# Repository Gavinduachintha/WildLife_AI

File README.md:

<div align="center">

# WildLife AI

</div>

## Introduction

WildLife AI is a prototype edge-computing system for monitoring remote forest environments. It uses computer vision on a Raspberry Pi 5 to identify objects or activities of interest, obtains the monitoring node's geographic position through a GPS module, and transmits a compact alert over a LoRa link.

The receiving station is based on a Raspberry Pi Pico 2. It receives the alert and presents the detected object, confidence value, geographic coordinates, and communication status on an IPS display. Detection is performed locally so that the system does not require continuous internet access or transmission of camera footage to a cloud service.

## Project Objectives

The system is intended to:

- detect selected objects in camera frames;
- associate detections with GPS coordinates;
- transmit detection data over a long-range, low-bandwidth radio link; and
- present received alerts at a separate monitoring station.

The project is intended for research and prototyping. It must not be treated as a certified safety, security, or emergency-response system.

## System Architecture

The system consists of two nodes.

The following diagram illustrates the connection between the remote monitoring node and the receiving station.

_Figure 1. System architecture of the WildLife AI monitoring and receiving nodes._

### Remote Monitoring Node

The remote node uses the following components:

- Raspberry Pi 5 (2 GB) for application execution and AI inference;
- Raspberry Pi Camera 3 NoIR for image acquisition;
- an object-detection model, currently represented by `yolov8n.pt`;
- NEO-6M GPS module for position acquisition; and
- SX1278 LoRa module for alert transmission.

The remote node captures images, performs inference, reads the GPS position when required, creates a detection message, and transmits the message through LoRa.

### Receiving Node

The receiving node uses the following components:

- Raspberry Pi Pico 2;
- SX1278 LoRa module; and
- 135 x 240 colour IPS display.

The receiving node obtains LoRa packets, processes the received fields, and updates the display with the available detection and status information.

## Detection and Communication Workflow

The expected operational sequence is:

1. The camera provides an image frame.
2. The Raspberry Pi 5 processes the frame and runs object detection.
3. If an object of interest is identified, the application obtains the current GPS position.
4. The application creates a detection message containing the object type, confidence value, latitude, longitude, and alert status.
5. The SX1278 transmitter sends the message over the LoRa link.
6. The Raspberry Pi Pico 2 receives and processes the message.
7. The receiving station displays the received information.

An example message is:

```text
OBJECT=HUMAN
CONF=0.91
LAT=XX.XXXX
LON=XX.XXXX
STATUS=ALERT
```

The exact message format and radio settings are defined by the implementation in the source files and receiver firmware.

## Hardware Requirements

| Component                  | Purpose                                      |
| -------------------------- | -------------------------------------------- |
| Raspberry Pi 5             | Edge processing and application execution    |
| Raspberry Pi Camera 3 NoIR | Image acquisition                            |
| SX1278 LoRa modules        | Wireless communication between the two nodes |
| NEO-6M GPS module          | Geographic position acquisition              |
| Raspberry Pi Pico 2        | Receiving station controller                 |
| 135 x 240 IPS display      | Alert and status presentation                |

The camera must be connected to the Raspberry Pi 5 through the CSI interface. The GPS module must be connected to the UART interface configured by the application. The LoRa modules must use compatible frequency, spreading factor, bandwidth, coding rate, sync word, and other radio parameters.

## Software Requirements

The project contains Python programs for the Raspberry Pi and an Arduino-compatible receiver program for the Raspberry Pi Pico 2. Python dependencies are listed in `requirements.txt`.

The following software is required for the Raspberry Pi implementation:

- Python 3;
- the packages listed in `requirements.txt`;
- Raspberry Pi camera support, including `rpicam-hello`; and
- access to the connected camera, GPS, and LoRa hardware.

The receiver requires the libraries and board configuration appropriate for the selected Raspberry Pi Pico 2 display and LoRa hardware.

## Installation

Clone the repository and enter its directory:

```bash
git clone https://github.com/Gavinduachintha/WildLife-AI.git
cd WildLife-AI
```

Create and activate a Python virtual environment:

```bash
python3 -m venv .venv
source .venv/bin/activate
```

Install the Python dependencies:

```bash
pip install -r requirements.txt
```

On Windows, activate the virtual environment with:

```powershell
.venv\Scripts\Activate.ps1
```

The hardware-dependent portions of the project are intended to run on the configured Raspberry Pi system. The virtual environment alone does not provide access to the camera, GPS, or LoRa hardware.

## Hardware Verification

Verify that the Raspberry Pi camera is available before starting the application:

```bash
rpicam-hello
```

Verify that the GPS module is connected to the configured UART interface and that it provides serial position data. Verify that both LoRa modules use matching radio settings and that the antenna and power configuration are suitable for the deployment.

## Running the Application

Start the main application on the Raspberry Pi 5 with:

```bash
python main.py
```

The application initializes the camera, GPS, LoRa interface, and detection model before entering the detection loop. The appropriate receiver firmware must be loaded onto the Raspberry Pi Pico 2 for alerts to be displayed.

## Repository Structure

The current repository contains:

```text
WildLifeAI/
├── Assets/
│   └── system_architecture.png
├── PCB Project/
│   ├── LoRa Tracker.kicad_pcb
│   ├── LoRa Tracker.kicad_pro
│   └── LoRa Tracker.kicad_sch
├── Receiver/
│   └── lora_rx_final_working_with_display.ino
├── cam2.py
├── cam3.py
├── camera1.py
├── detect.py
├── detect1.py
├── Final.py
├── gpsTest.py
├── main.py
├── requirements.txt
├── yolov8n.pt
└── README.md
```

Some Python files are experimental or provide separate hardware tests. `main.py` is the documented application entry point. The receiver firmware is located in `Receiver/`, and the KiCad design files are located in `PCB Project/`.

## Communication Range

The project uses a target communication range of approximately 5 to 10 km. This is not a guaranteed operating distance. Actual performance depends on antenna configuration, terrain, vegetation, obstacles, transmit power, frequency, spreading factor, bandwidth, coding rate, and receiver sensitivity.

## Limitations

Detection performance depends on the model, training data, lighting, camera position, object distance and size, occlusion, and environmental conditions. The system may produce false positives or false negatives.

LoRa is a low-bandwidth communication method and is appropriate for compact detection messages rather than continuous video. Communication reliability and range must be tested under the conditions of the intended deployment.

The project is a prototype. Hardware compatibility, electrical safety, radio compliance, data protection, and operational reliability must be evaluated before any field deployment.

## Author

Gavindu Achintha

## Contact

For project-related questions or contributions, contact the author through [GitHub](https://github.com/Gavinduachintha).

## License

The project license has not been specified in the current repository.

---

<p align="center">
	<strong>WildLife AI</strong><br>
	Edge monitoring for remote environments<br>
	<a href="https://github.com/Gavinduachintha">Gavindu Achintha on GitHub</a>
</p>

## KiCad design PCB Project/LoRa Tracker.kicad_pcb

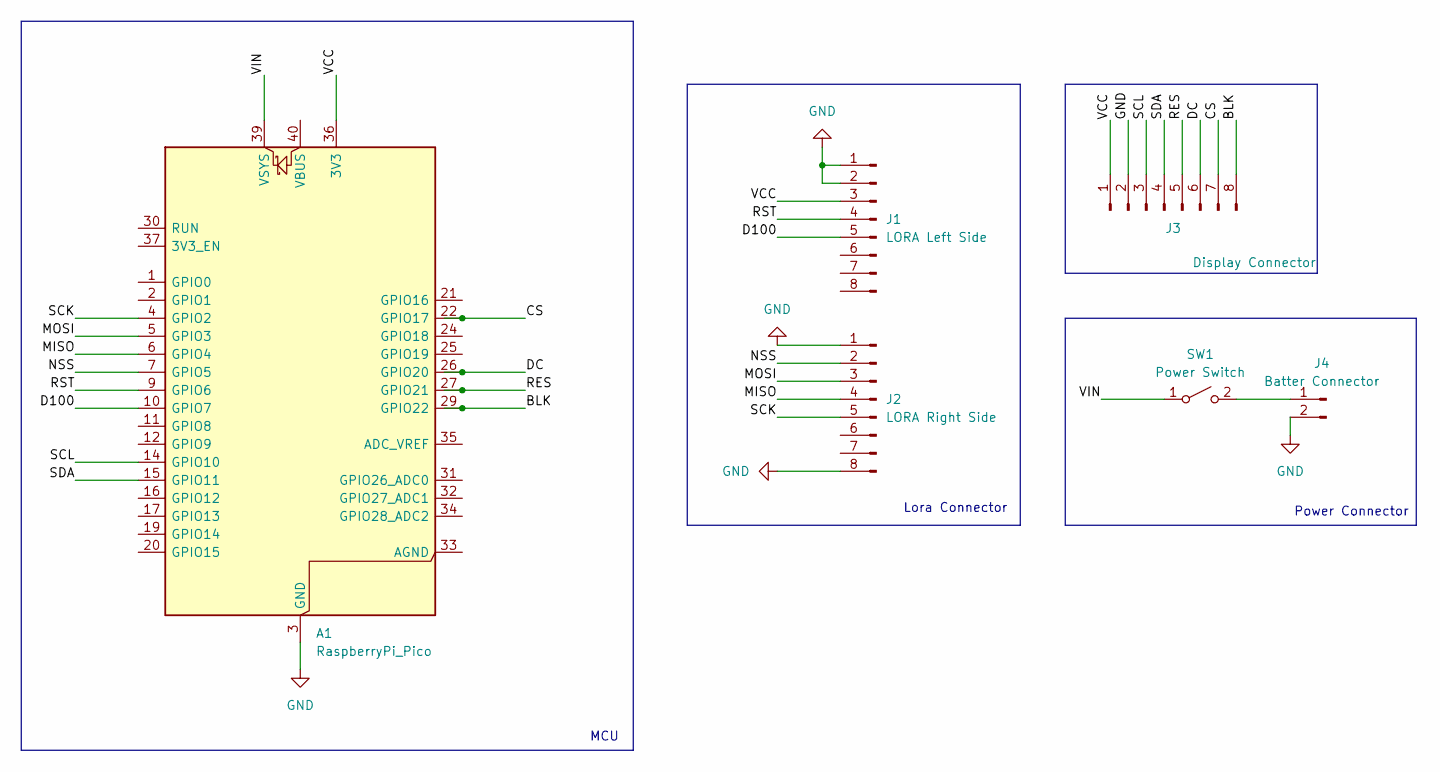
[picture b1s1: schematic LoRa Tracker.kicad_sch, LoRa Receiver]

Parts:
A1: RaspberryPi_Pico; RaspberryPi_Pico_Common_Unspecified
J1: LORA Left Side; PinHeader_1x08_P2.54mm_Vertical
J2: LORA Right Side; PinHeader_1x08_P2.54mm_Vertical
J3: Display Connector; PinHeader_1x08_P2.54mm_Vertical
J4: Batter Connector; JST_EH_B2B-EH-A_1x02_P2.50mm_Vertical
SW1: Power Switch; SW_DIP_SPSTx01_Slide_9.78x4.72mm_W7.62mm_P2.54mm

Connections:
/BLK: A1.29 (GPIO22), J3.8
/CS: A1.22 (GPIO17), J3.7
/D100: A1.10 (GPIO7), J1.5
/DC: A1.26 (GPIO20), J3.6
/MISO: A1.6 (GPIO4), J2.4
/MOSI: A1.5 (GPIO3), J2.3
/NSS: A1.7 (GPIO5), J2.2
/RES: A1.27 (GPIO21), J3.5
/RST: A1.9 (GPIO6), J1.4
/SCK: A1.4 (GPIO2), J2.5
/SCL: A1.14 (GPIO10), J3.3
/SDA: A1.15 (GPIO11), J3.4
/VCC: A1.36 (3V3), J1.3, J3.1
/VIN: A1.39 (VSYS), SW1.1 (A)
GND: A1.3 (GND), A1.8 (GND), A1.13 (GND), A1.18 (GND), A1.23 (GND), A1.28 (GND), A1.38 (GND), J1.1, J1.2, J2.1, J2.8, J3.2, J4.2
unnamed: J4.1, SW1.2 (B)

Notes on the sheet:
MCU
Lora Connector
Power Connector

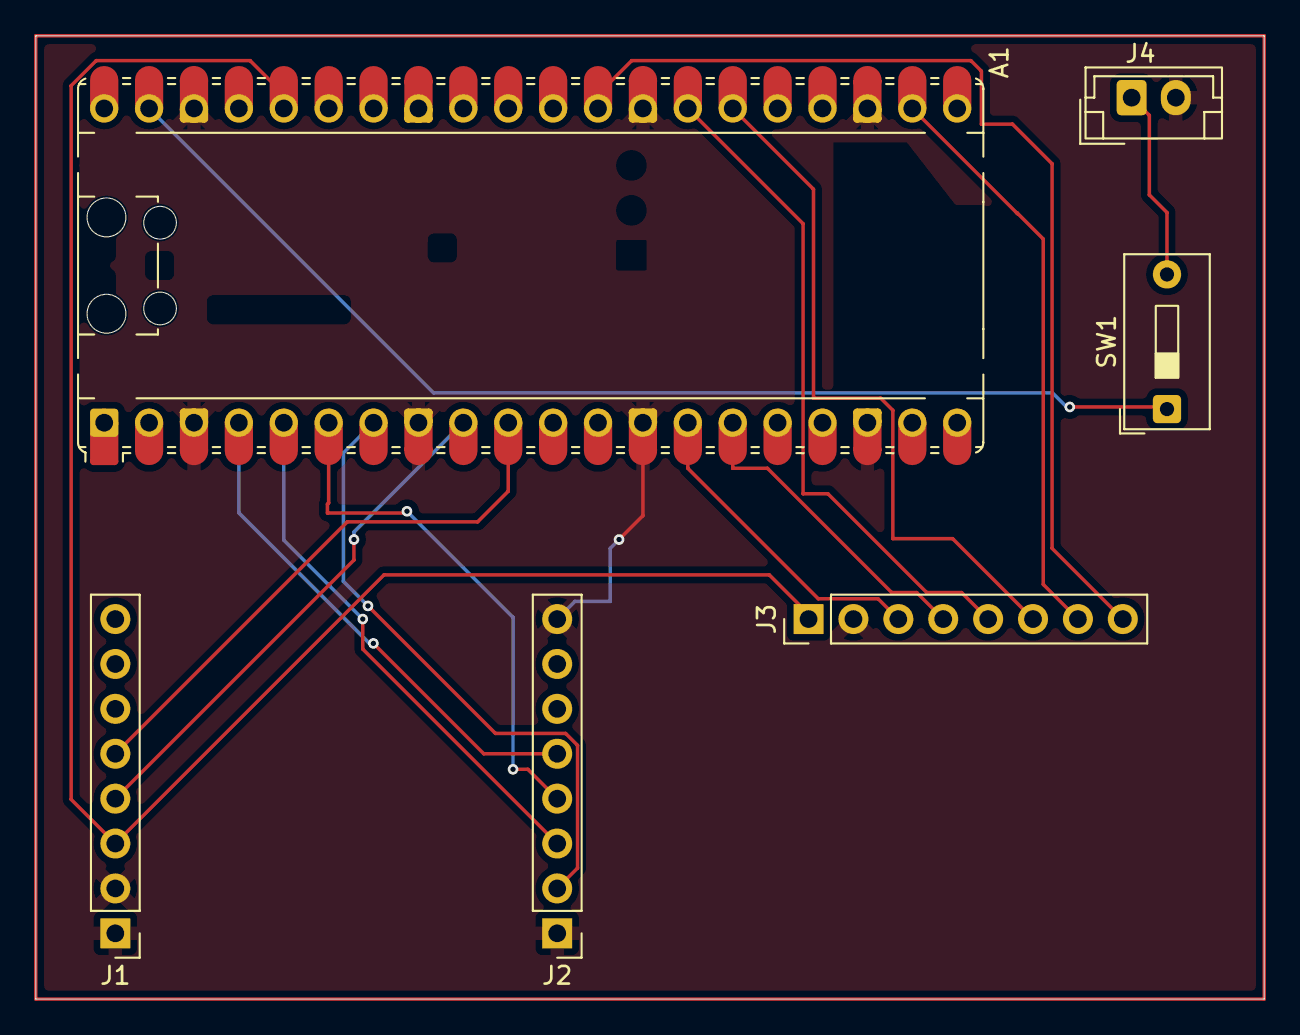
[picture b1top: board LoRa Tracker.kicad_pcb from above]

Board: 2 copper layers, 69.5 x 54.5 mm, 6 parts (0 on the bottom side), 16 nets.
